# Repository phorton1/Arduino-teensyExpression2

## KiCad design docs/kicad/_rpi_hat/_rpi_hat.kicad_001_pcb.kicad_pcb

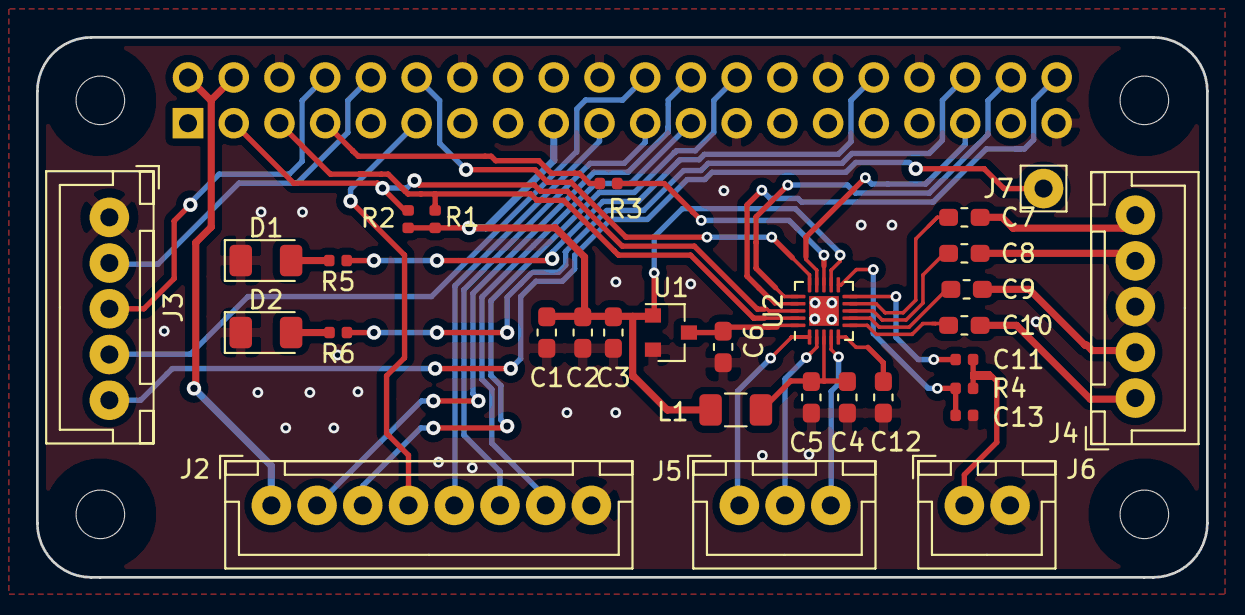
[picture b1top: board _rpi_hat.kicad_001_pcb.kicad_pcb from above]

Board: 2 copper layers, 65.0 x 30.0 mm, 35 parts (1 on the bottom side), 42 nets.

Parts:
C1, C4, C6, C7, C8, C9, C10: 2.2uf; C_0603_1608Metric_Pad1.05x0.95mm_HandSolder
C2, C3, C5: 0.1uf; C_0603_1608Metric_Pad1.05x0.95mm_HandSolder
C11: 0.1uf; C_0402_1005Metric
C12: 0.15uf; C_0603_1608Metric_Pad1.05x0.95mm_HandSolder
C13: 2.2uf; C_0402_1005Metric
D1, D2: LED; LED_1206_3216Metric
H1, H2, H3, H4: MountingHole; MountingHole_2.7mm_M2.5_uHAT_RPi
J1: GPIO_CONNECTOR; PinSocket_2x20_P2.54mm_Vertical_Centered_Anchor
J2: display; myJSTx08
J3: esp32; myJSTx05
J4: audio; myJSTx05
J5: HP; myJSTx03
J6: mic; myJSTx02
J7: RPI_RUN; myPinHeader_1x01
L1: Ferrite 600; L_1206_3216Metric
R1, R2, R4, R5, R6: 2.2k; R_0402_1005Metric
R3: 100; R_0402_1005Metric
U1: AP7313-18; SOT-23
U2: pauls_sgtl_5000_20; QFN-20-1EP_3x3mm_P0.4mm_EP1.65x1.65mm

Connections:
+3V3: C1.1, C2.1, C3.1, J1.1, J1.17, L1.1, R1.1, R2.1, U1.1, U2.12
+5V: J1.2, J1.4, J2.1
GND: C1.2, C2.2, C3.2, C4.2, C5.2, C6.2, C12.2, C13.2, D1.1, D2.1, J1.6, J1.9, J1.14, J1.20, J1.25, J1.30, J1.34, J1.39, J2.8, J3.1, J4.3, J6.2, U1.2, U2.21
HP_GND: J5.2, U2.2
HP_L: J5.3, U2.4
HP_R: J5.1, U2.1
I2S_RX_ACTIVE: J1.32, R5.1
I2S_TX_ACTIVE: J1.36, R6.1
LED_CS: J1.24, J2.2
LINEIN_L: C7.2, J4.5
LINEIN_R: C8.2, J4.4
LINEOUT_L: C9.2, J4.2
LINEOUT_R: C10.2, J4.1
MIC_IN: C11.2, J6.1, R4.2
MISO: J1.21, J2.6
MOSI: J1.19, J2.5
unnamed: C4.1, C5.1, L1.2, U2.3
unnamed: C6.1, U1.3, U2.20
unnamed: C7.1, U2.9
unnamed: C8.1, U2.8
unnamed: C9.1, U2.7
unnamed: C10.1, U2.6
unnamed: C11.1, U2.10
unnamed: C12.1, U2.5
unnamed: C13.1, R4.1, U2.11
unnamed: D1.2, R5.2
unnamed: D2.2, R6.2
unnamed: R3.2, U2.13
RPI_READY: J1.22, J3.4
RPI_RUN: J3.5, J7.1
RPI_RX: J1.10, J3.2
RPI_TX: J1.8, J3.3
SCL: J1.5, R1.2, U2.19
SCLK: J1.23, J2.7
SDA: J1.3, R2.2, U2.18
SGTL_BLCK: J1.12, U2.15
SGTL_FCLK: J1.35, U2.14
SGTL_I2S_IN: J1.40, U2.17
SGTL_I2S_OUT: J1.38, U2.16
SGTL_MCLK: J1.7, R3.1
TFT_CD: J1.11, J2.4
TOUCH_CS: J1.26, J2.3

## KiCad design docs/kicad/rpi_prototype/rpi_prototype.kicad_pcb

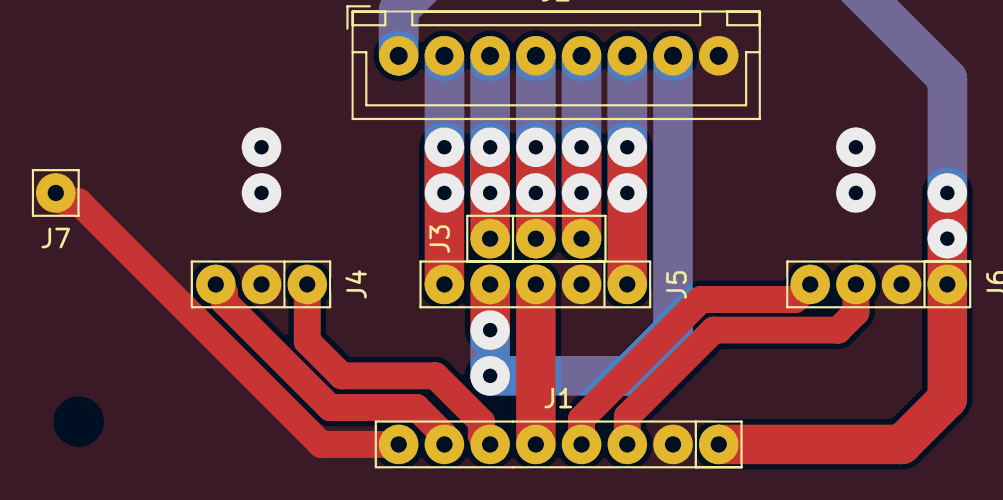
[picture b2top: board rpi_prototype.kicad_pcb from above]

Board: 2 copper layers, 7 parts (0 on the bottom side), 14 nets.

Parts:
J1: Teensy3.2; my8Pin
J2: Display; myJSTx08
J3: PI_3; invPinSocket_1x03
J4: PI_2; invPinSocket_1x03
J5: PI_1; invPinSocket_1x5
J6: PI_0; invPinSocket_1x04
J7: PI_RUN; my1pin

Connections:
+5V: J1.1, J2.1, J6.1
AUDIO_RX_ACTIVE: J1.6, J4.1
AUDIO_TX_ACTIVE: J1.7, J4.3
DISPLAY_CD: J2.6, J5.1
DISPLAY_CS: J2.7, J5.4
DISPLAY_MISO: J2.4, J3.2
DISPLAY_MOSI: J2.5, J3.3
DISPLAY_SCLK: J2.3, J3.1
GND: J1.2, J2.8, J4.2, J5.2, J6.2
RPI_READY: J1.5, J5.3
RPI_RUN: J1.8, J7.1
RPI_RX0: J1.4, J6.4
RPI_TX0: J1.3, J6.3
TOUCH_CS: J2.2, J5.5

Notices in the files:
docs/kicad/_rpi_hat/_rpi_hat.kicad_001_pcb.kicad_pcb:
This PCB design is licensed under MIT Open Source License.
